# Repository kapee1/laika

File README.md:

# Laika - 45%-ish v4n4g0n-inspired keyboard  

### Build guide — *coming soon*

---

### Main features:

* Custom compact layout — 47 keys + half of number row
* Waveshare RP2040-Zero MCU
* MX hotswap
* Split spacebar support (2 × 3u or 1 x 6u)
* Two plate options: Standard and Extra (extra plate has enlarged stabilizers holes)
* Top mount with o-rings
* The two halves of the case and top weight are held together by magnets
* VIAL / QMK firmware

---

### Layout:

---

## BOM:

| Part | Quantity |
|------|----------|
| Laika PCB | 1 |
| Laika Case Top | 1 |
| Laika Case Bottom | 1 |
| Laika Plate (Standard or Extra) | 1 |
| Top Weight | 1 |
| Battery Cover (optional) | 1 |
| Waveshare RP2040-Zero | 1 |
| 1N4148W SOD-123 Diodes | 53 |
| MX-compatible switches | 53 |
| MX hotswap sockets | 53 |
| Stabilizers (PCB-mount) | 2x3u or 1x6u |
| M2 screws x 4 mm | 10 |
| M2 inserts OD:3.2, H:3 | 8 |
| Rubber feet 3M SJ5302 (8x8x2) | 4 |
| Magnets 5x3 | 14 |
| Magnets 5x1 | 4 |
| Silicone o-rings 5x2 | 8 |

---

## Files:

```
laika/
├── case/
│   ├── top.step                          # Top case
│   ├── bottom.step                       # Bottom case
│   ├── battery-cover.step                # Battery cover
│   ├── standart-plate.step               # Standard plate
│   ├── extra-plate.step                  # Extra plate
│   ├── top-weight (laika).step           # Top weight — "laika" text
│   └── top-weight (laika-the-keyboard).step  # Top weight — "laika the keyboard" text
├── laika-pcb/
│   ├── laika-pcb.kicad_pcb               # PCB layout (KiCad 10)
│   ├── laika-pcb.kicad_sch               # Schematic (KiCad 10)
│   ├── laika-pcb.kicad_pro               # KiCad project
│   └── Production files/
│       └── Laika PCB gerbers.zip         # Ready-to-order gerber files
└── plate-dxf/
    ├── standart-plate.dxf                # Standard plate for laser cutting / CNC
    └── extra-plate.dxf                   # Extra plate with enlarged stabilizers cutouts / CNC
```

---

## PCB manufacturing:

Send `laika-pcb/Production files/Laika PCB gerbers.zip` to your preferred PCB manufacturer (JLCPCB, PCBWay, etc.) with the following settings:

| Setting | Value |
|---------|-------|
| Layers | 2 |
| Thickness | 1.6 mm |
| Surface finish | HASL / ENIG |
| Color | your choice |

---

## Firmware:

Laika runs on **VIAL** (QMK fork with real-time key remapping — no flashing required for layout changes.

https://github.com/vial-kb/vial-qmk/tree/vial/keyboards/laika

**Flashing (RP2040-Zero):**
1. Hold the BOOT button on the RP2040-Zero while connecting USB.
2. A drive named `RPI-RP2` will appear.
3. Drop the `.uf2` firmware file onto that drive.
4. The keyboard will reboot and be ready to use.

---

## What is tested?

| Part | Is tested? |
|---------|-------|
| Top | Changed since proto, untested ⚠️ |
| Bottom | Changed since proto, untested ⚠️ |
| Standart plate | ✅  |
| Extra plate | Untested ⚠️ |
| Top weight | ✅ |
| PCB | ✅ |
| Battery cover | ✅ |

---

## Photos of PC proto:

---

*Named after Laika — the first living creature to orbit Earth.*

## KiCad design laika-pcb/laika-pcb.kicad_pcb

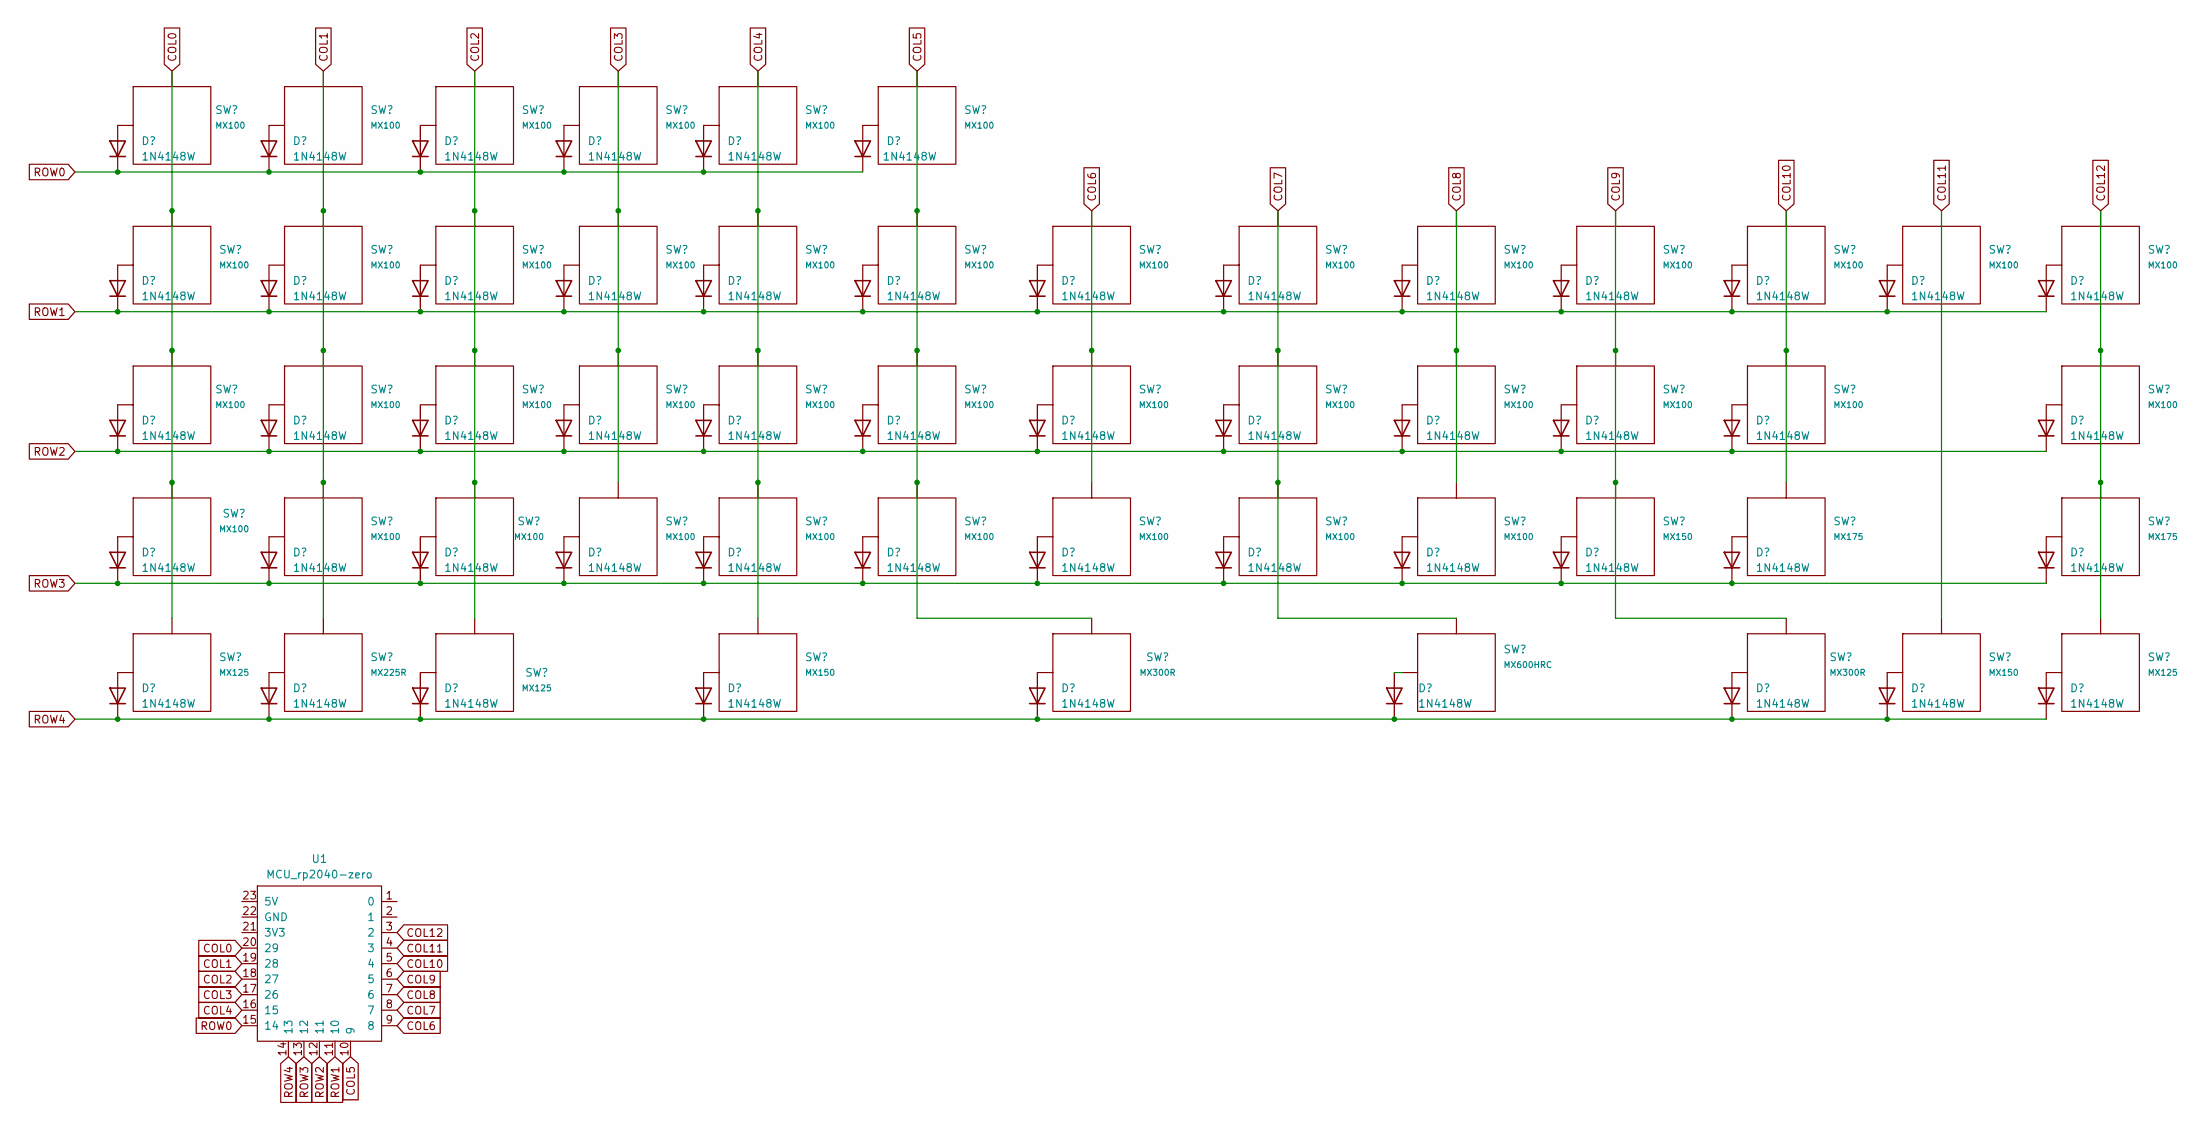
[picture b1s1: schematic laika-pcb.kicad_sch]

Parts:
D1, D2, D3, D4, D5, D6, D7, D8, D9, D10, D11, D12, D13, D14, D15, D16, D17, D18, D19, D20, D21, D22, D23, D24, D25, D26, D27, D28, D29, D30, D31, D32, D33, D34, D35, D36, D37, D38, D39, D40, D41, D42, D43, D44, D45, D46, D47, D48, D49, D50, D51, D52: 1N4148W; D_SOD-123
SW1, SW2, SW3, SW4, SW5, SW6, SW8, SW9, SW10, SW11, SW12, SW13, SW14, SW15, SW16, SW17, SW18, SW19, SW21, SW22, SW23, SW24, SW25, SW26, SW27, SW28, SW29, SW30, SW33, SW34, SW35, SW36, SW37, SW38, SW39, SW40: MX100; MX100H
SW7: MX100; MX150H
SW20, SW31: MX100; MX175H
SW32: MX100; MX200HR
SW41, SW51: MX150; MX100H
SW42: MX175; MX100H
SW43: MX175; MX150H
SW44, SW52: MX125; MX125H
SW45: MX225R; MX100H
SW46: MX125; MX150H
SW47: MX150; MX300HR
SW48: MX300R; MX600HRС
SW49: MX600HRC; MX300HR
SW50: MX300R; MX150H
U1: MCU_rp2040-zero; MCU_rp2040-zero-smd_reversed

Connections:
COL0: SW1.2 (Row), SW7.2 (Row), SW20.2 (Row), SW32.2 (Row), SW44.2 (Row), U1.20 (29); also elsewhere on the board
COL1: SW2.2 (Row), SW8.2 (Row), SW21.2 (Row), SW33.2 (Row), SW45.2 (Row), U1.19 (28)
COL2: SW3.2 (Row), SW9.2 (Row), SW22.2 (Row), SW34.2 (Row), SW46.2 (Row), U1.18 (27)
COL3: SW4.2 (Row), SW10.2 (Row), SW23.2 (Row), SW35.2 (Row), U1.17 (26)
COL4: SW5.2 (Row), SW11.2 (Row), SW24.2 (Row), SW36.2 (Row), SW47.2 (Row), U1.16 (15)
COL5: SW6.2 (Row), SW12.2 (Row), SW25.2 (Row), SW37.2 (Row), SW48.2 (Row), U1.10 (9)
COL6: SW13.2 (Row), SW26.2 (Row), SW38.2 (Row), U1.9 (8)
COL7: SW14.2 (Row), SW27.2 (Row), SW39.2 (Row), SW49.2 (Row), U1.8 (7)
COL8: SW15.2 (Row), SW28.2 (Row), SW40.2 (Row), U1.7 (6)
COL9: SW16.2 (Row), SW29.2 (Row), SW41.2 (Row), SW50.2 (Row), U1.6 (5)
COL10: SW17.2 (Row), SW30.2 (Row), SW42.2 (Row), U1.5 (4)
COL11: SW18.2 (Row), SW51.2 (Row), U1.4 (3)
COL12: SW19.2 (Row), SW31.2 (Row), SW43.2 (Row), SW52.2 (Row), U1.3 (2)
unnamed: D1.2 (A), SW1.1 (Col)
unnamed: D2.2 (A), SW2.1 (Col)
unnamed: D3.2 (A), SW3.1 (Col)
unnamed: D4.2 (A), SW4.1 (Col)
unnamed: D5.2 (A), SW5.1 (Col)
unnamed: D6.2 (A), SW6.1 (Col)
unnamed: D7.2 (A), SW7.1 (Col)
unnamed: D8.2 (A), SW8.1 (Col)
unnamed: D9.2 (A), SW9.1 (Col)
unnamed: D10.2 (A), SW10.1 (Col)
unnamed: D11.2 (A), SW11.1 (Col)
unnamed: D12.2 (A), SW12.1 (Col)
unnamed: D13.2 (A), SW13.1 (Col)
unnamed: D14.2 (A), SW14.1 (Col)
unnamed: D15.2 (A), SW15.1 (Col)
unnamed: D16.2 (A), SW16.1 (Col)
unnamed: D17.2 (A), SW17.1 (Col)
unnamed: D18.2 (A), SW18.1 (Col)
unnamed: D19.2 (A), SW19.1 (Col)
unnamed 32: D20.2 (A), SW20.1 (Col); also elsewhere on the board
unnamed: D21.2 (A), SW21.1 (Col)
unnamed: D22.2 (A), SW22.1 (Col)
unnamed: D23.2 (A), SW23.1 (Col)
unnamed: D24.2 (A), SW24.1 (Col)
unnamed: D25.2 (A), SW25.1 (Col)
unnamed: D26.2 (A), SW26.1 (Col)
unnamed: D27.2 (A), SW27.1 (Col)
unnamed: D28.2 (A), SW28.1 (Col)
unnamed: D29.2 (A), SW29.1 (Col)
unnamed: D30.2 (A), SW30.1 (Col)
unnamed: D31.2 (A), SW31.1 (Col)
unnamed: D32.2 (A), SW32.1 (Col)
unnamed: D33.2 (A), SW33.1 (Col)
unnamed: D34.2 (A), SW34.1 (Col)
unnamed: D35.2 (A), SW35.1 (Col)
unnamed: D36.2 (A), SW36.1 (Col)
unnamed: D37.2 (A), SW37.1 (Col)
unnamed: D38.2 (A), SW38.1 (Col)
unnamed: D39.2 (A), SW39.1 (Col)
unnamed: D40.2 (A), SW40.1 (Col)
unnamed: D41.2 (A), SW41.1 (Col)
unnamed: D42.2 (A), SW42.1 (Col)
unnamed: D43.2 (A), SW43.1 (Col)
unnamed: D44.2 (A), SW44.1 (Col)
unnamed: D45.2 (A), SW45.1 (Col)
unnamed: D46.2 (A), SW46.1 (Col)
unnamed: D47.2 (A), SW47.1 (Col)
unnamed: D48.2 (A), SW48.1 (Col)
unnamed: D49.2 (A), SW49.1 (Col)
unnamed: D50.2 (A), SW50.1 (Col)
unnamed: D51.2 (A), SW51.1 (Col)
unnamed: D52.2 (A), SW52.1 (Col)
ROW0: D1.1 (K), D2.1 (K), D3.1 (K), D4.1 (K), D5.1 (K), D6.1 (K), U1.15 (14)
ROW1: D7.1 (K), D8.1 (K), D9.1 (K), D10.1 (K), D11.1 (K), D12.1 (K), D13.1 (K), D14.1 (K), D15.1 (K), D16.1 (K), D17.1 (K), D18.1 (K), D19.1 (K), U1.11 (10)
ROW2: D20.1 (K), D21.1 (K), D22.1 (K), D23.1 (K), D24.1 (K), D25.1 (K), D26.1 (K), D27.1 (K), D28.1 (K), D29.1 (K), D30.1 (K), D31.1 (K), U1.12 (11)
ROW3: D32.1 (K), D33.1 (K), D34.1 (K), D35.1 (K), D36.1 (K), D37.1 (K), D38.1 (K), D39.1 (K), D40.1 (K), D41.1 (K), D42.1 (K), D43.1 (K), U1.13 (12)
ROW4: D44.1 (K), D45.1 (K), D46.1 (K), D47.1 (K), D48.1 (K), D49.1 (K), D50.1 (K), D51.1 (K), D52.1 (K), U1.14 (13)

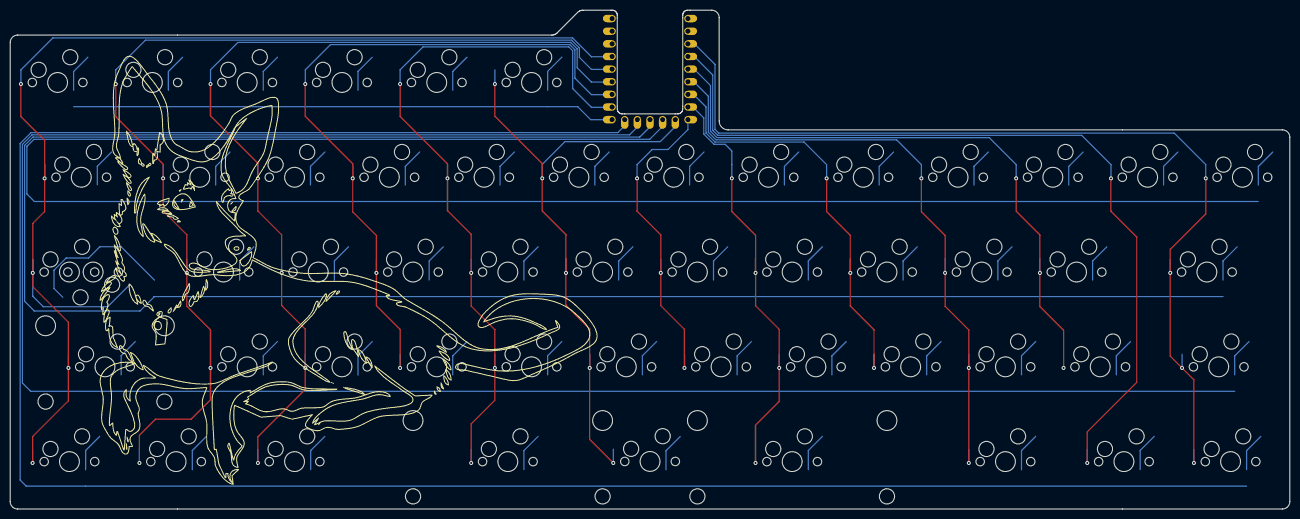
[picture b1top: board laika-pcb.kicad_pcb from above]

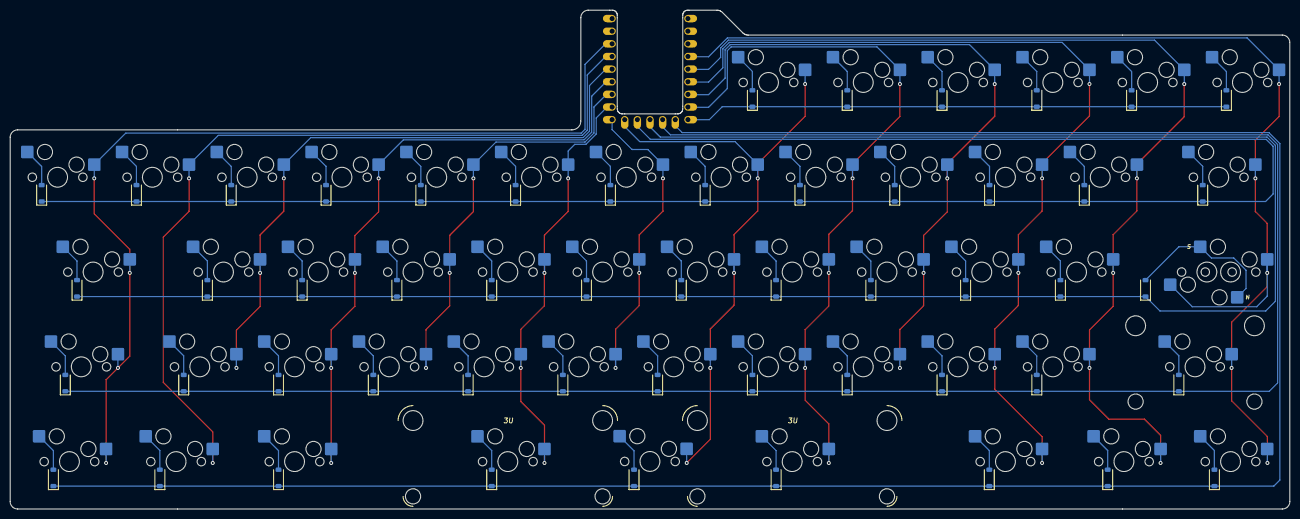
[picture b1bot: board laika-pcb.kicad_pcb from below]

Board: 2 copper layers, 257.2 x 100.2 mm, 106 parts (52 on the bottom side), 70 nets.

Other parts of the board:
SW53: MXH125; MX125H

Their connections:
COL0: SW53.2; also elsewhere on the board
unnamed 32: SW53.1; also elsewhere on the board

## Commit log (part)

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2026-04-09 Revise README for Laika keyboard specifications
    Updated README with new images, feature list, and BOM details.
2026-04-09 Revise README to include top mount and magnet details
    Updated features and specifications in the README.
2026-04-14 small fixes in top and bottom
2026-04-14 added the builded firmware
2026-04-14 Enhance README with detailed specifications and testing info
    Updated README with additional details on plate options, M2 inserts, and testing status.
2026-04-14 Clean up README
2026-04-14 Update README with additional images and note
